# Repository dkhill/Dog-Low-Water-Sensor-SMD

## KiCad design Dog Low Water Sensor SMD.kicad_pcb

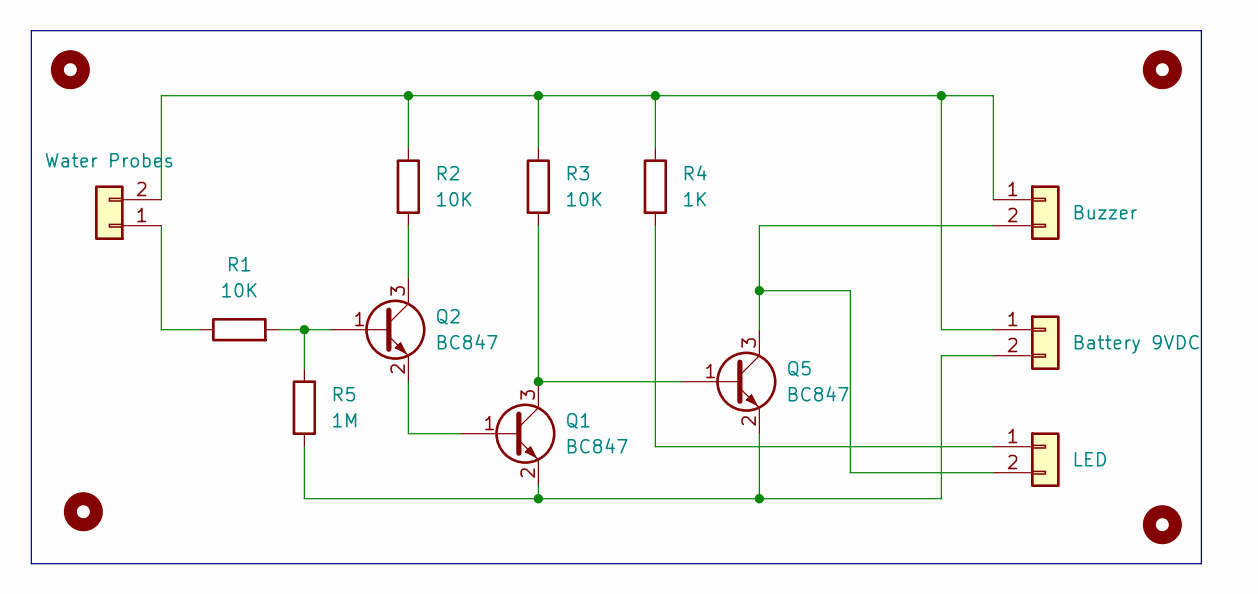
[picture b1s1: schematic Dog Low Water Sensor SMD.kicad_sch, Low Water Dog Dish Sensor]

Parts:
H1, H2, H3, H4: MountingHole; MountingHole_2.5mm
J1: Water Probes; SolderWire-0.25sqmm_1x02_P4.5mm_D0.65mm_OD2mm
J2: Battery 9VDC; SolderWire-0.25sqmm_1x02_P4.5mm_D0.65mm_OD2mm
J3: Buzzer; SolderWire-0.25sqmm_1x02_P4.5mm_D0.65mm_OD2mm
J4: LED; SolderWire-0.25sqmm_1x02_P4.5mm_D0.65mm_OD2mm
Q1, Q2, Q5: BC847; SOT-23
R1, R2, R3: 10K; R_0603_1608Metric
R4: 1K; R_0603_1608Metric
R5: 1M; R_0603_1608Metric

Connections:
unnamed: J1.1, R1.1
unnamed: J1.2, J2.1, J3.1, R2.1, R3.1, R4.1
unnamed: J2.2, Q1.2 (E), Q5.2 (E), R5.2
unnamed: J3.2, J4.2, Q5.3 (C)
unnamed: J4.1, R4.2
unnamed: Q1.1 (B), Q2.2 (E)
unnamed: Q1.3 (C), Q5.1 (B), R3.2
unnamed: Q2.1 (B), R1.2, R5.1
unnamed: Q2.3 (C), R2.2

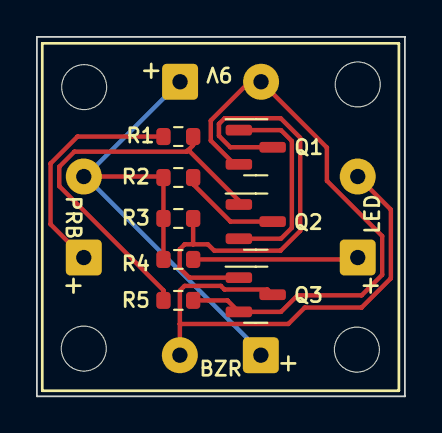
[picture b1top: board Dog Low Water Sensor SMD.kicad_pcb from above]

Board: 2 copper layers, 20.4 x 20.0 mm, 16 parts (0 on the bottom side), 9 nets.

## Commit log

2023-08-27 Initial Commit 202308271613
